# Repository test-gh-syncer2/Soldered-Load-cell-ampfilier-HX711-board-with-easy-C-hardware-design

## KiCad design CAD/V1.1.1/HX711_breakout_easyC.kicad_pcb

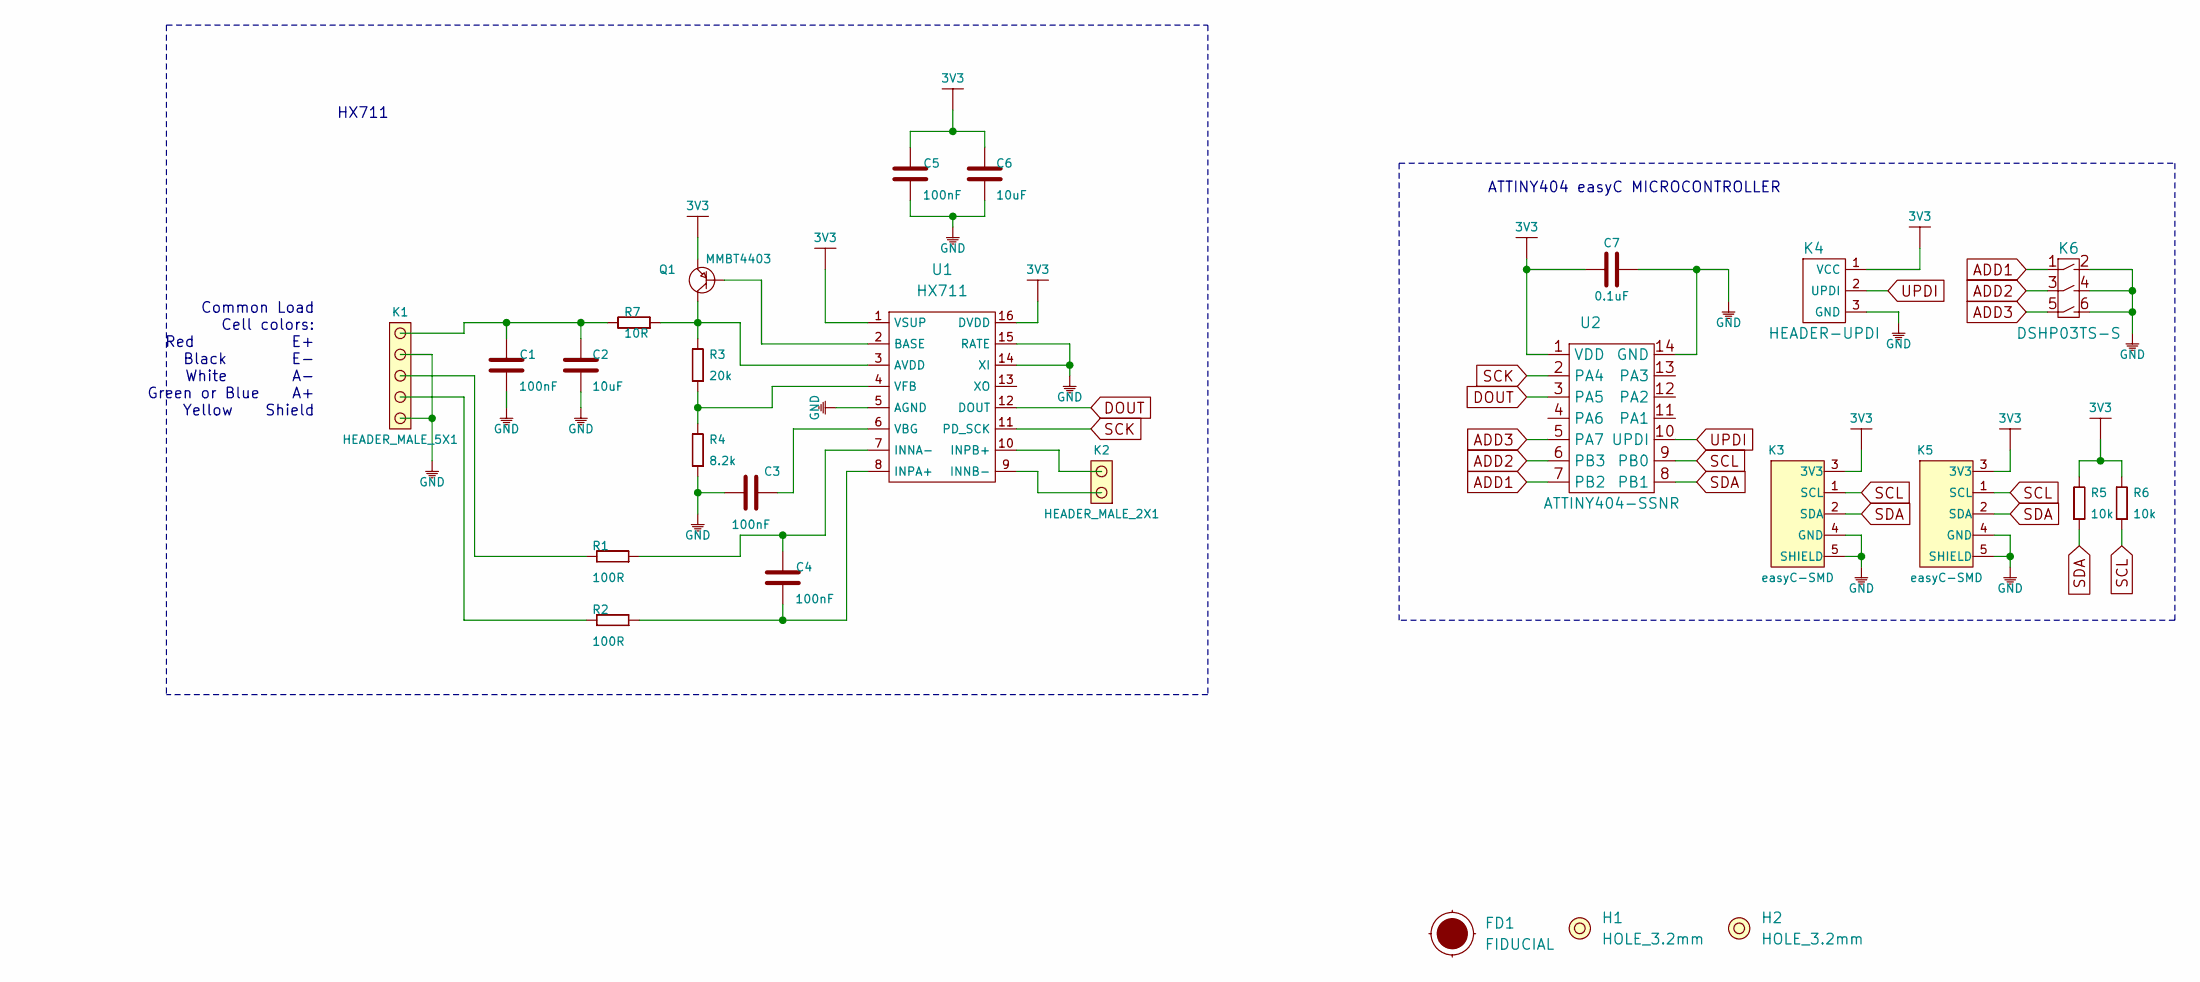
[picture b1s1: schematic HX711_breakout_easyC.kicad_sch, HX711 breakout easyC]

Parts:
C1, C3, C4, C5: 100nF; 0603C
C2, C6: 10uF; 1206C
C7: 0.1uF; 0603C
FD1: FIDUCIAL; FIDUCIAL_23
H1, H2: HOLE_3.2mm
K1: HEADER_MALE_5X1
K2: HEADER_MALE_2X1
K3, K5: easyC-SMD; easyC-connector
K4: HEADER-UPDI
K6: DSHP03TS-S
Q1: MMBT4403; SOT-23-3
R1, R2: 100R; 0603R
R3: 20k; 0603R
R4: 8.2k; 0603R
R5, R6: 10k; 0603R
R7: 10R; 0603R
U1: HX711; SOP-16
U2: ATTINY404-SSNR; SOIC-14

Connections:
3V3: C5.2, C6.2, C7.1, K3.3 (3V3), K4.1 (VCC), K5.3 (3V3), Q1.2 (E), R5.2, R6.2, U1.1 (VSUP), U1.16 (DVDD), U2.1 (VDD)
ADD1: K6.1, U2.7 (PB2)
ADD2: K6.3, U2.6 (PB3)
ADD3: K6.5, U2.5 (PA7)
DOUT: U1.12 (DOUT), U2.3 (PA5)
GND: C1.1, C2.1, C3.1, C5.1, C6.1, C7.2, K1.1, K1.4, K3.4 (GND), K3.5 (SHIELD), K4.3 (GND), K5.4 (GND), K5.5 (SHIELD), K6.2, K6.4, K6.6, R4.1, U1.5 (AGND), U1.14 (XI), U1.15 (RATE), U2.14 (GND)
unnamed: C1.2, C2.2, K1.5, R7.2
unnamed: C3.2, U1.6 (VBG)
unnamed: C4.1, R2.1, U1.8 (INPA+)
unnamed: C4.2, R1.1, U1.7 (INNA-)
unnamed: K1.2, R2.2
unnamed: K1.3, R1.2
unnamed: K2.1, U1.9 (INNB-)
unnamed: K2.2, U1.10 (INPB+)
unnamed: Q1.1 (B), U1.2 (BASE)
unnamed: Q1.3 (C), R3.2, R7.1, U1.3 (AVDD)
unnamed: R3.1, R4.2, U1.4 (VFB)
SCK: U1.11 (PD_SCK), U2.2 (PA4)
SCL: K3.1 (SCL), K5.1 (SCL), R6.1, U2.9 (PB0)
SDA: K3.2 (SDA), K5.2 (SDA), R5.1, U2.8 (PB1)
UPDI: K4.2 (UPDI), U2.10 (UPDI)

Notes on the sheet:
Common Load Cell colors: Red E+ Black E- White A- Green or Blue A+ Yellow Shield
HX711
ATTINY404 easyC MICROCONTROLLER

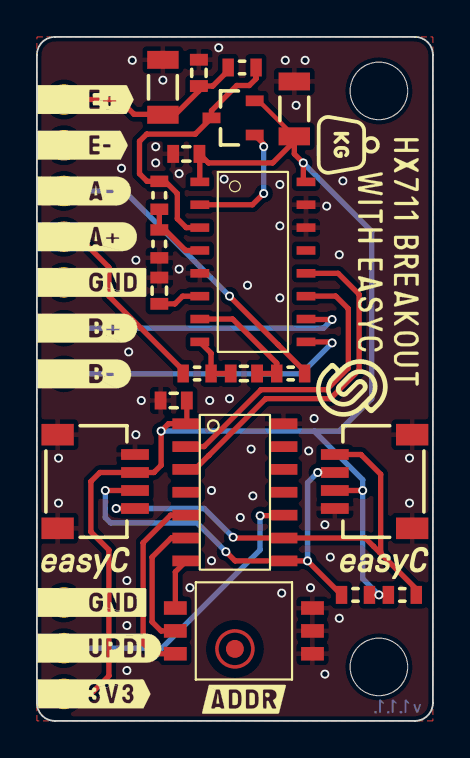
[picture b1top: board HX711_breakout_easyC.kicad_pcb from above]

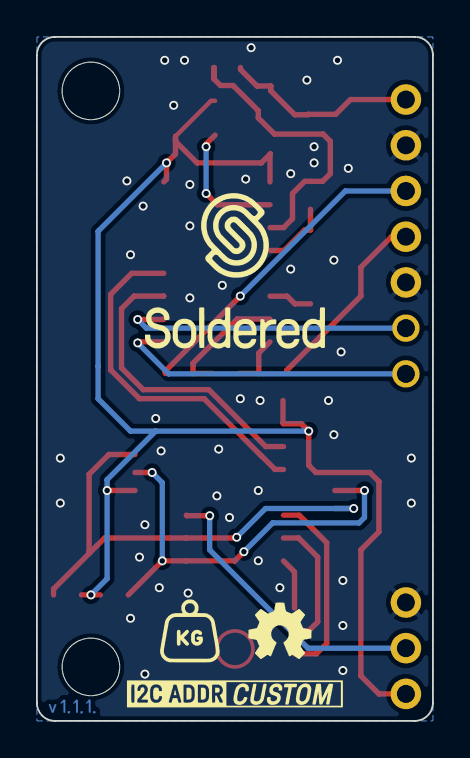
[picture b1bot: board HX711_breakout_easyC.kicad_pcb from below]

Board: 2 copper layers, 22.0 x 38.0 mm, 26 parts (2 on the bottom side), 21 nets.

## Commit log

2021-09-23 Syncing to git
2021-09-23 Updating open source files.
